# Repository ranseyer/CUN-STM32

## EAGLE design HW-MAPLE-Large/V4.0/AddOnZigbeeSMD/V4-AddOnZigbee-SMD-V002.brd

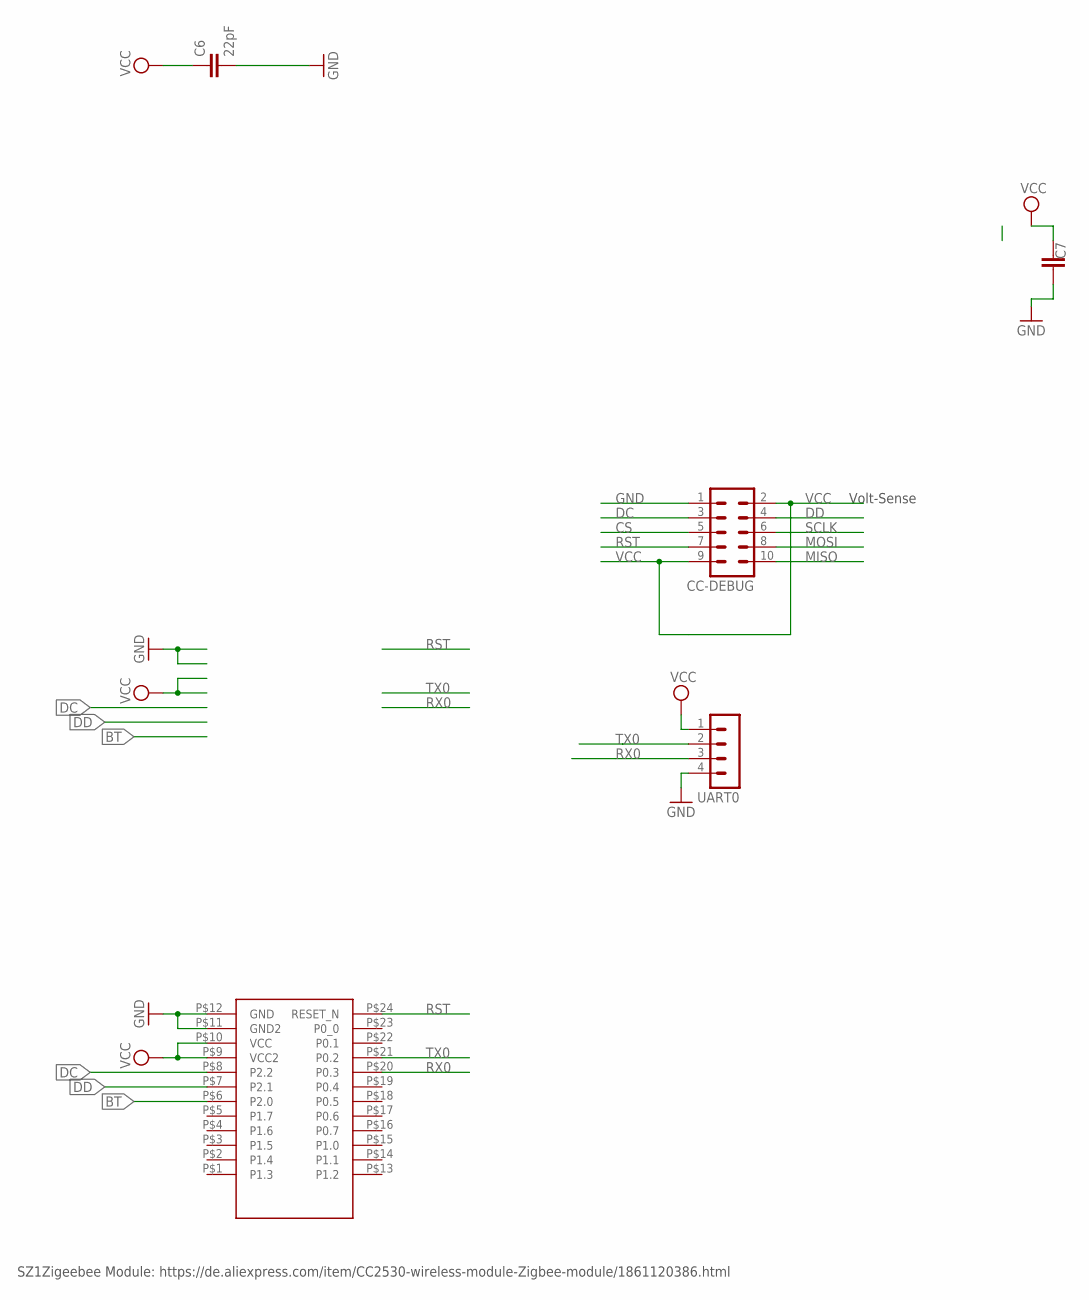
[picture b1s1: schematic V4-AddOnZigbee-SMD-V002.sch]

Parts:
C6: 22pF; C0805
C7: C-EUC1812; C1812
CC-DEBUG: MA05-2
U$1: CC2530; SZ1ZIGBEE-SMD
UART0: MA04-1

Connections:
BT: U$1.P$6 (P2.0)
CS: CC-DEBUG.5
DC: CC-DEBUG.3, U$1.P$8 (P2.2)
DD: CC-DEBUG.4, U$1.P$7 (P2.1)
GND: C6.2, C7.1, CC-DEBUG.1, U$1.P$11 (GND2), U$1.P$12 (GND), UART0.4
MISO: CC-DEBUG.10
MOSI: CC-DEBUG.8
RST: CC-DEBUG.7, U$1.P$24 (RESET_N)
RX0: U$1.P$20 (P0.3), UART0.3
SCLK: CC-DEBUG.6
TX0: U$1.P$21 (P0.2), UART0.2
VCC: C6.1, C7.2, CC-DEBUG.2, CC-DEBUG.9, U$1.P$9 (VCC2), U$1.P$10 (VCC), UART0.1

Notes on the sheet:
Volt-Sense
SZ1Zigeebee Module: https://de.aliexpress.com/item/CC2530-wireless-module-Zigbee-module/1861120386.html

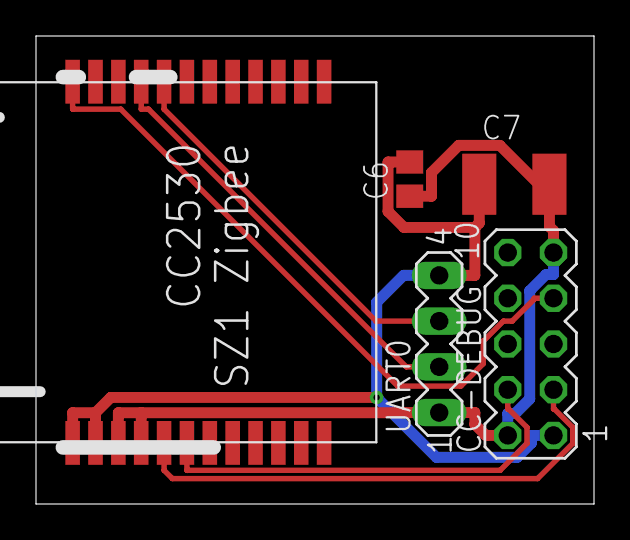
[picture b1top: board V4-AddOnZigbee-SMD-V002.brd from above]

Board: 2 copper layers, 31.0 x 26.0 mm, 5 parts (0 on the bottom side), 7 nets.

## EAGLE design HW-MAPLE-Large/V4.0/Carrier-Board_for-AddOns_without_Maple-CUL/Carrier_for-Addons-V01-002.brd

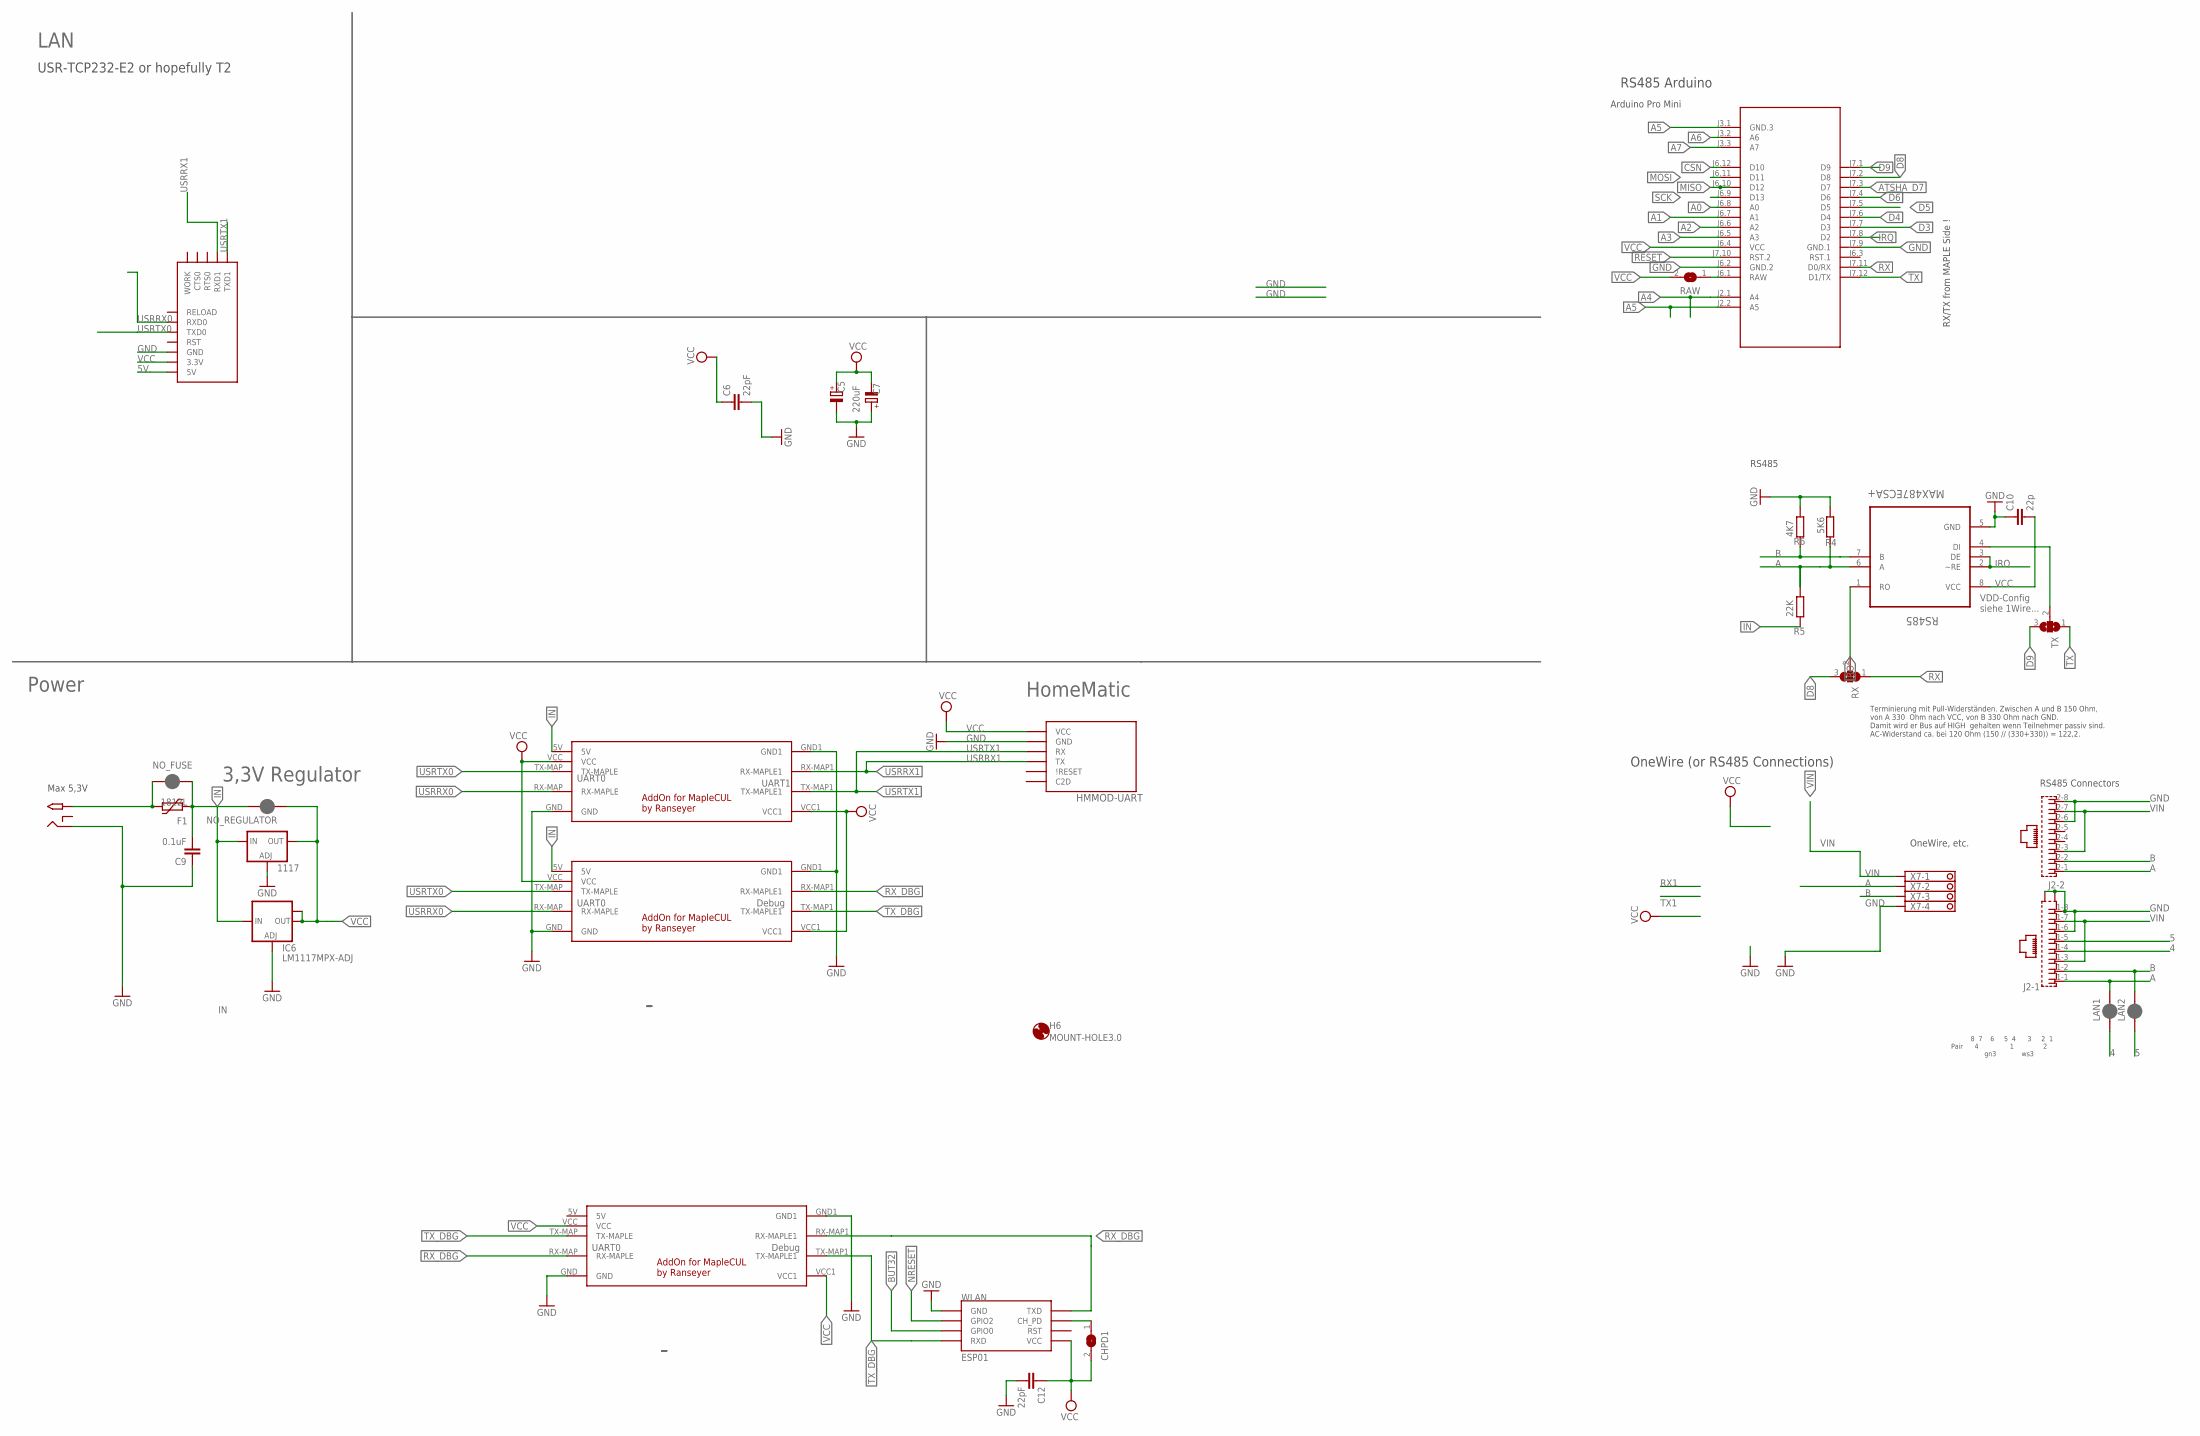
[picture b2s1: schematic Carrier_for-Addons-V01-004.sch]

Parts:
1117: LD117ADT50TR; DPACK
C5: 220uF; E5-8,5
C6, C12: 22pF; C0805
C7: CPOL-EUSMCE; SMC_E
C9: 0.1uF; C1206
C10: 22p; C0805
CHPD1: SJ
F1: 1812L
H6: MOUNT-HOLE3.0; 3,0
HMMOD-UART: HM-MOD-UARTDIL; HM-MOD-UART-DIL
IC6: LM1117MPX-ADJ; SOT223
J2: RJ45_2X_S
LAN1, LAN2: JUMPER-SMT_2_NC_PASTE_SILK; SMT-JUMPER_2_NC_PASTE_SILK
M1: ARDUINO-PRO-MINI-3.3V#NP; ARDUINO-PRO-MINI#NP
NO_FUSE: JUMPER-SMT_2_NC_PASTE_NO-SILK; SMT-JUMPER_2_NC_PASTE_NO-SILK
NO_REGULATOR: JUMPER-SMT_2_NC_PASTE_NO-SILK; SMT-JUMPER_2_NC_PASTE_NO-SILK
R4: 5K6; R0805
R5: 22K; R0805
R6: 4K7; R0805
RAW: SJ
RS485: MAX487ECSA+; SOIC127P600X175-8N
RX: SJ2W; SJ_2
TX: SJ2W; SJ_2
U$1, U$3, U$4: MAPLE-CUL-ADDON-V01; MAPLE-CUL-V01
U$2: 2.1MMJACKTHM; PJ-102A
U$5: USR-TCP232-E2
WLAN: ESP01
X7: 1751264

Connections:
4: J2.1-4 (4), LAN1.1
5: J2.1-5 (5), LAN2.1
5V.: U$5.5V
A: J2.1-1 (1), J2.2-1 (1), LAN1.2, R4.2, R5.2, RS485.6 (A), X7.2
A0: M1.J6.8 (A0)
A1: M1.J6.7 (A1)
A2: M1.J6.6 (A2)
A3: M1.J6.5 (A3)
A4: M1.J2.1 (A4)
A5: M1.J2.2 (A5), M1.J3.1 (GND.3)
A6: M1.J3.2 (A6)
A7: M1.J3.3 (A7)
ATSHA_D7: M1.J7.3 (D7)
B: J2.1-2 (2), J2.2-2 (2), LAN2.2, R6.1, RS485.7 (B), X7.3
BUT32: WLAN.GPIO0
CSN: M1.J6.12 (D10)
D3: M1.J7.7 (D3)
D4: M1.J7.6 (D4)
D5: M1.J7.5 (D5)
D6: M1.J7.4 (D6)
D8: M1.J7.2 (D8), RX.3
D9: M1.J7.1 (D9), TX.3
DI1: RS485.4 (DI), TX.2
GND: 1117.1 (ADJ), C5.-, C6.2, C7.+, C9.1, C10.1, C12.2, HMMOD-UART.2 (GND), IC6.1 (ADJ), J2.1-6 (6), J2.1-8 (8), J2.2-6 (6), J2.2-8 (8), J2.G1 (S2), J2.G3 (S1), M1.J6.2 (GND.2), M1.J7.9 (GND.1), R4.1, R6.2, RS485.5 (GND), U$1.GND, U$1.GND1, U$2.RING, U$3.GND, U$3.GND1, U$4.GND, U$4.GND1, U$5.GND, WLAN.GND, X7.4
IN: 1117.3 (IN), C9.2, F1.P$1 (1), IC6.3 (IN), NO_FUSE.1, NO_REGULATOR.2, R5.1, U$3.5V, U$4.5V
IRQ: M1.J7.8 (D2), RS485.2 (~RE), RS485.3 (DE)
MISO: M1.J6.10 (D12)
MOSI: M1.J6.11 (D11)
unnamed: CHPD1.1, WLAN.CH_PD
NRESET: WLAN.GPIO2
RAW1: M1.J6.1 (RAW), RAW.1
RESET: M1.J7.10 (RST.2)
RO: RS485.1 (RO), RX.2
RX: M1.J7.11 (D0/RX), RX.1
RX_DBG: U$1.RX-MAP (RX-MAPLE), U$1.RX-MAP1 (RX-MAPLE1), U$4.RX-MAP1 (RX-MAPLE1), WLAN.TX (TXD)
SCK: M1.J6.9 (D13)
TX: M1.J7.12 (D1/TX), TX.1
TX_DBG: U$1.TX-MAP (TX-MAPLE), U$1.TX-MAP1 (TX-MAPLE1), U$4.TX-MAP1 (TX-MAPLE1), WLAN.RX (RXD)
USRRX0: U$3.RX-MAP (RX-MAPLE), U$4.RX-MAP (RX-MAPLE), U$5.RXD0
USRRX1: HMMOD-UART.5 (TX), U$3.RX-MAP1 (RX-MAPLE1), U$5.RXD1
USRTX0: U$3.TX-MAP (TX-MAPLE), U$4.TX-MAP (TX-MAPLE), U$5.TXD0
USRTX1: HMMOD-UART.6 (RX), U$3.TX-MAP1 (TX-MAPLE1), U$5.TXD1
VCC: 1117.4 (OUT), C5.+, C6.1, C7.-, C10.2, C12.1, CHPD1.2, HMMOD-UART.1 (VCC), IC6.2 (OUT), IC6.TAB (OUT1), M1.J6.4 (VCC), NO_REGULATOR.1, RAW.2, RS485.8 (VCC), U$1.VCC, U$1.VCC1, U$3.VCC, U$3.VCC1, U$4.VCC, U$4.VCC1, U$5.3.3V, WLAN.VCC
VIN: F1.P$2 (2), J2.1-3 (3), J2.1-7 (7), J2.2-3 (3), J2.2-7 (7), NO_FUSE.2, U$2.TIP, X7.1

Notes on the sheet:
Power
HomeMatic
LAN
UART0
Debug
UART1
RX/TX from MAPLE Side !
8 7 6 5 4 3 2 1 Pair 4 1 2 gn3 ws3
RS485 Connectors
OneWire, etc.
Arduino Pro Mini
RS485
VDD-Config siehe 1Wire...
Terminierung mit Pull-Widerständen. Zwischen A und B 150 Ohm, von A 330 Ohm nach VCC, von B 330 Ohm nach GND. Damit wird er Bus auf HIGH gehalten wenn Teilnehmer passiv sind. AC-Widerstand ca. bei 120 Ohm (150 // (330+330)) = 122,2.
OneWire (or RS485 Connections)
USR-TCP232-E2 or hopefully T2
RS485 Arduino
Max 5,3V
3,3V Regulator

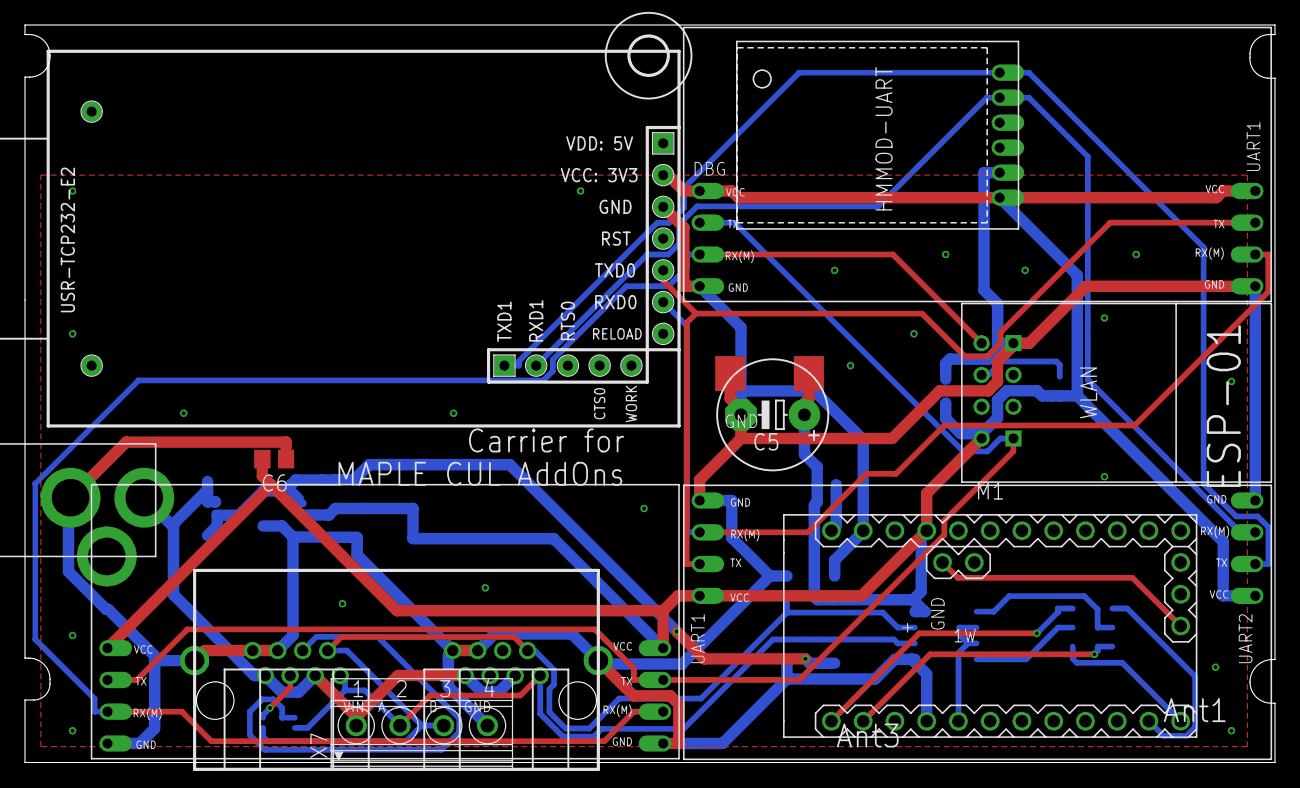
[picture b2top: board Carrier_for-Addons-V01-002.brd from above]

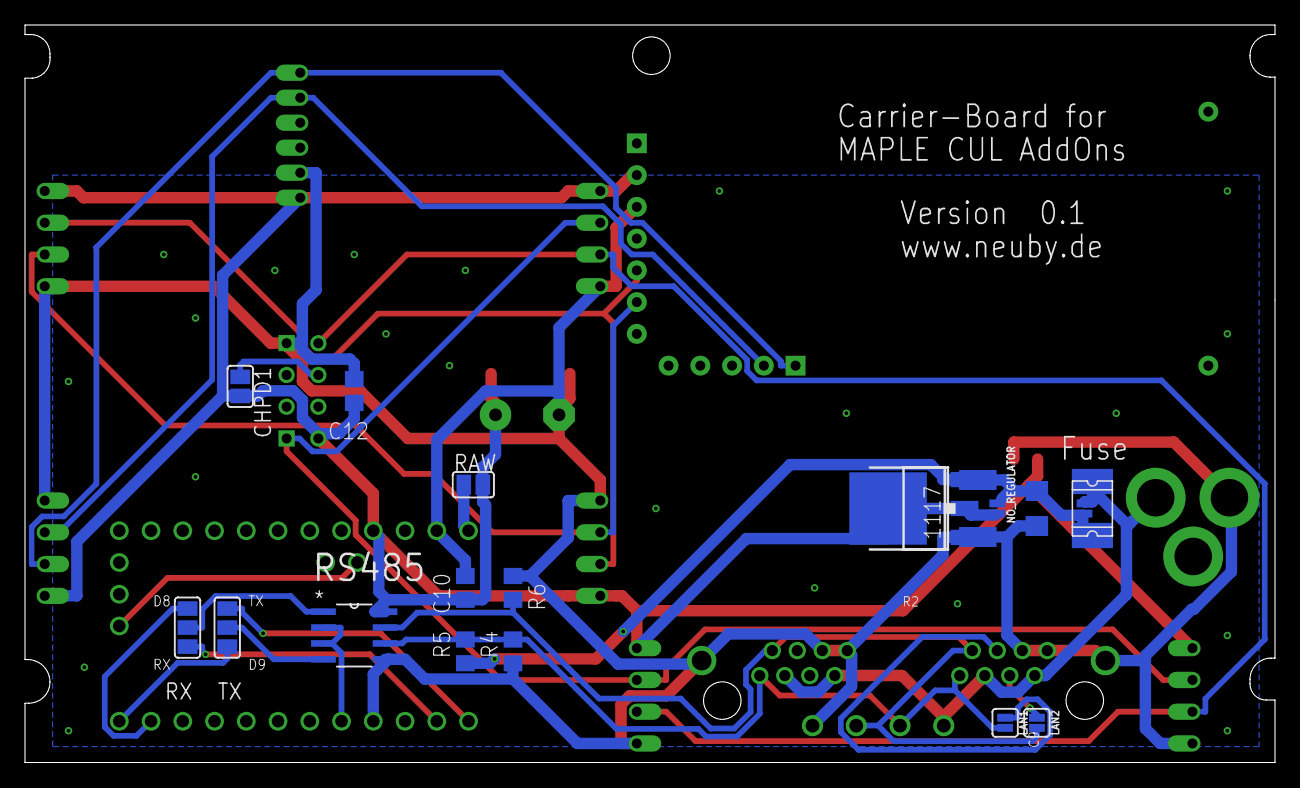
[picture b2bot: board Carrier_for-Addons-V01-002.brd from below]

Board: 2 copper layers, 100.0 x 59.0 mm, 32 parts (18 on the bottom side), 24 nets.

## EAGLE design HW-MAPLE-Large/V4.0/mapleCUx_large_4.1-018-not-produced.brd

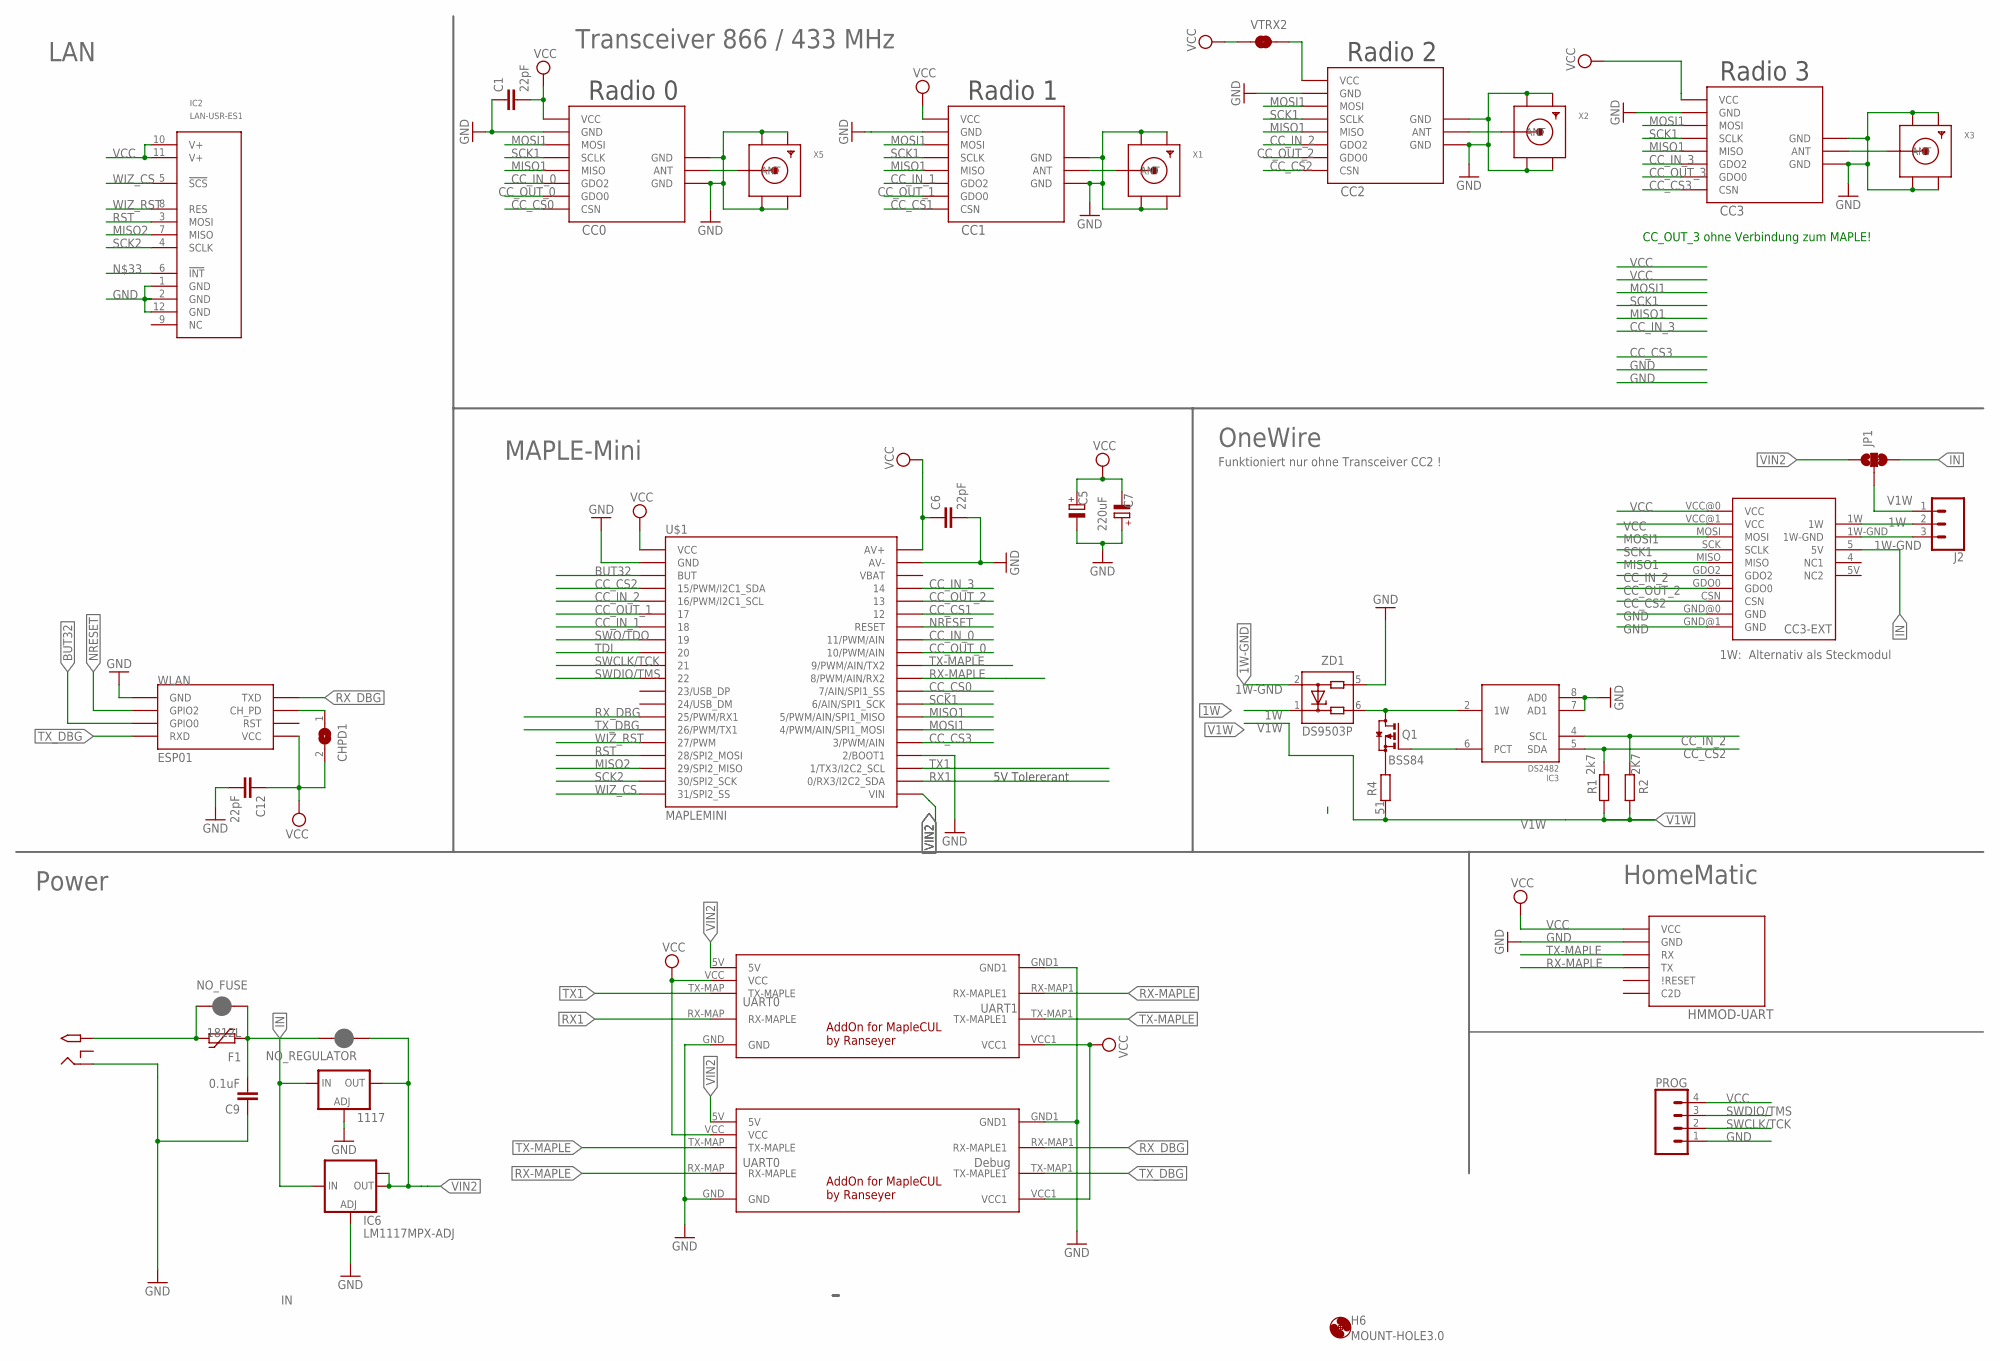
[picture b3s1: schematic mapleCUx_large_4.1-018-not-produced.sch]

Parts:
1117: LD117ADT50TR; DPACK
C1, C6, C12: 22pF; C0805
C5: 220uF; E5-8,5
C7: CPOL-EUSMCE; SMC_E
C9: 0.1uF; C1206
CC0: CC1101; CC1101_MODULE1_SMD
CC1, CC2, CC3: CC1101_MODULE1SMD; CC1101_MODULE1_SMD
CC3-EXT: ONEWIRE-MODULE; ONEWIRE_CC1101_MODULE3_DIL
CHPD1: SJ
F1: 1812L
H6: MOUNT-HOLE3.0; 3,0
HMMOD-UART: HM-MOD-UARTDIL; HM-MOD-UART-DIL
IC2: LAN-USR-ES1; USR-ES1
IC3: DS2482; SO08
IC6: LM1117MPX-ADJ; SOT223
J2: CONN_03LONGPADS; 1X03_LONGPADS
JP1: JUMPER-SMT_3_1-NC_TRACE_SILK; SMT-JUMPER_3_1-NC_TRACE_SILK
NO_FUSE: JUMPER-SMT_2_NC_PASTE_NO-SILK; SMT-JUMPER_2_NC_PASTE_NO-SILK
NO_REGULATOR: JUMPER-SMT_2_NC_PASTE_NO-SILK; SMT-JUMPER_2_NC_PASTE_NO-SILK
PROG: CONN_04LOCK; 1X04_LOCK
Q1: BSS84; SOT23
R1: 2k7; R0805
R2: 2K7; R0805
R4: 51; R0805
U$1: MAPLEMINI; 20-DIP
U$2: 2.1MMJACKTHM; PJ-102A
U$3, U$4: MAPLE-CUL-ADDON-V01; MAPLE-CUL-V01
VTRX2: JUMPER-SMT_2_NC_TRACE_SILK; SMT-JUMPER_2_NC_TRACE_SILK
WLAN: ESP01
X1, X2, X3, X5: SMACONNECTOR_EDGE; SMA_EDGELAUNCH
ZD1: DS9503P; TSOC6

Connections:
1W: CC3-EXT.1W, J2.2, ZD1.1
1W-GND: CC3-EXT.1W-GND, J2.3, ZD1.2
ANT0: CC0.ANT, X5.P (ANT)
ANT1: CC1.ANT, X1.P (ANT)
ANT2: CC2.ANT, X2.P (ANT)
ANT3: CC3.ANT, X3.P (ANT)
BUT32: U$1.3 (BUT), WLAN.GPIO0
CC_CS0: CC0.CSN, U$1.29 (7/AIN/SPI1_SS)
CC_CS1: CC1.CSN, U$1.35 (12)
CC_CS2: CC2.CSN, CC3-EXT.CSN, IC3.5 (SDA), R1.2, U$1.4 (15/PWM/I2C1_SDA)
CC_CS3: CC3.CSN, U$1.25 (3/PWM/AIN)
CC_IN_0: CC0.GDO2, U$1.33 (11/PWM/AIN)
CC_IN_1: CC1.GDO2, U$1.7 (18)
CC_IN_2: CC2.GDO2, CC3-EXT.GDO2, IC3.4 (SCL), R2.2, U$1.5 (16/PWM/I2C1_SCL)
CC_IN_3: CC3.GDO2, U$1.37 (14)
CC_OUT_0: CC0.GDO0, U$1.32 (10/PWM/AIN)
CC_OUT_1: CC1.GDO0, U$1.6 (17)
CC_OUT_2: CC2.GDO0, CC3-EXT.GDO0, U$1.36 (13)
CC_OUT_3: CC3.GDO0
GND: 1117.1 (ADJ), C1.1, C5.-, C6.2, C7.+, C9.1, C12.2, CC0.GND@0 (GND), CC0.GND@1 (GND), CC0.GND@2 (GND), CC1.GND@0 (GND), CC1.GND@1 (GND), CC1.GND@2 (GND), CC2.GND@0 (GND), CC2.GND@1 (GND), CC2.GND@2 (GND), CC3.GND@0 (GND), CC3.GND@1 (GND), CC3.GND@2 (GND), CC3-EXT.GND@0 (GND), CC3-EXT.GND@1 (GND), HMMOD-UART.2 (GND), IC2.1 (GND), IC2.2 (GND), IC2.12 (GND), IC3.3 (GND), IC3.7 (AD1), IC3.8 (AD0), IC6.1 (ADJ), PROG.1, U$1.2 (GND), U$1.24 (2/BOOT1), U$1.39 (AV-), U$2.RING, U$3.GND, U$3.GND1, U$4.GND, U$4.GND1, WLAN.GND, X1.GND@1 (GND4), X1.GND@2 (GND3), X1.GND@3 (GND2), X1.GND@4 (GND1), X2.GND@1 (GND4), X2.GND@2 (GND3), X2.GND@3 (GND2), X2.GND@4 (GND1), X3.GND@1 (GND4), X3.GND@2 (GND3), X3.GND@3 (GND2), X3.GND@4 (GND1), X5.GND@1 (GND4), X5.GND@2 (GND3), X5.GND@3 (GND2), X5.GND@4 (GND1), ZD1.5
IN: 1117.3 (IN), C9.2, CC3-EXT.5 (5V), F1.P$1 (1), IC6.3 (IN), JP1.3, NO_FUSE.1, NO_REGULATOR.2
MISO1: CC0.MISO, CC1.MISO, CC2.MISO, CC3.MISO, CC3-EXT.MISO, U$1.27 (5/PWM/AIN/SPI1_MISO)
MISO2: IC2.7 (MISO), U$1.18 (29/SPI2_MISO)
MOSI1: CC0.MOSI, CC1.MOSI, CC2.MOSI, CC3.MOSI, CC3-EXT.MOSI, U$1.26 (4/PWM/AIN/SPI1_MOSI)
unnamed: CC2.VCC, VTRX2.2
unnamed: CHPD1.1, WLAN.CH_PD
unnamed: IC3.6 (PCT), Q1.1 (G)
unnamed: IC3.2 (1W), Q1.3 (D), ZD1.6
unnamed: Q1.2 (S), R4.1
NRESET: U$1.34 (RESET), WLAN.GPIO2
RST: IC2.3 (MOSI), U$1.17 (28/SPI2_MOSI)
RX1: U$1.22 (0/RX3/I2C2_SDA), U$3.RX-MAP (RX-MAPLE)
RX-MAPLE: HMMOD-UART.5 (TX), U$1.30 (8/PWM/AIN/RX2), U$3.RX-MAP1 (RX-MAPLE1), U$4.RX-MAP (RX-MAPLE)
RX_DBG: U$1.14 (25/PWM/RX1), U$4.RX-MAP1 (RX-MAPLE1), WLAN.TX (TXD)
SCK1: CC0.SCLK, CC1.SCLK, CC2.SCLK, CC3.SCLK, CC3-EXT.SCK (SCLK), U$1.28 (6/AIN/SPI1_SCK)
SCK2: IC2.4 (SCLK), U$1.19 (30/SPI2_SCK)
SWCLK/TCK: PROG.2, U$1.10 (21)
SWDIO/TMS: PROG.3, U$1.11 (22)
SWO/TDO: U$1.8 (19)
TDI: U$1.9 (20)
TX1: U$1.23 (1/TX3/I2C2_SCL), U$3.TX-MAP (TX-MAPLE)
TX-MAPLE: HMMOD-UART.6 (RX), U$1.31 (9/PWM/AIN/TX2), U$3.TX-MAP1 (TX-MAPLE1), U$4.TX-MAP (TX-MAPLE)
TX_DBG: U$1.15 (26/PWM/TX1), U$4.TX-MAP1 (TX-MAPLE1), WLAN.RX (RXD)
V1W: IC3.1 (VDD), J2.1, JP1.2, R1.1, R2.1, R4.2
VCC: C1.2, C5.+, C6.1, C7.-, C12.1, CC0.VCC, CC1.VCC, CC3.VCC, CC3-EXT.VCC@0 (VCC), CC3-EXT.VCC@1 (VCC), CHPD1.2, HMMOD-UART.1 (VCC), IC2.10 (V+), IC2.11 (V+), PROG.4, U$1.1 (VCC), U$1.40 (AV+), U$3.VCC, U$3.VCC1, U$4.VCC, U$4.VCC1, VTRX2.1, WLAN.VCC
VIN: F1.P$2 (2), NO_FUSE.2, U$2.TIP
VIN2: 1117.4 (OUT), IC6.2 (OUT), IC6.TAB (OUT1), JP1.1, NO_REGULATOR.1, U$1.21 (VIN), U$3.5V, U$4.5V
WIZ_CS: IC2.5 (!SCS!), U$1.20 (31/SPI2_SS)
WIZ_RST: IC2.8 (RES), U$1.16 (27/PWM)

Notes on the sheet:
Radio 1
Radio 0
Radio 2
Radio 3
OneWire
Power
HomeMatic
MAPLE-Mini
Transceiver 866 / 433 MHz
LAN
CC_OUT_3 ohne Verbindung zum MAPLE!
Funktioniert nur ohne Transceiver CC2 !
1W: Alternativ als Steckmodul
UART0
Debug
UART1
5V Tolererant

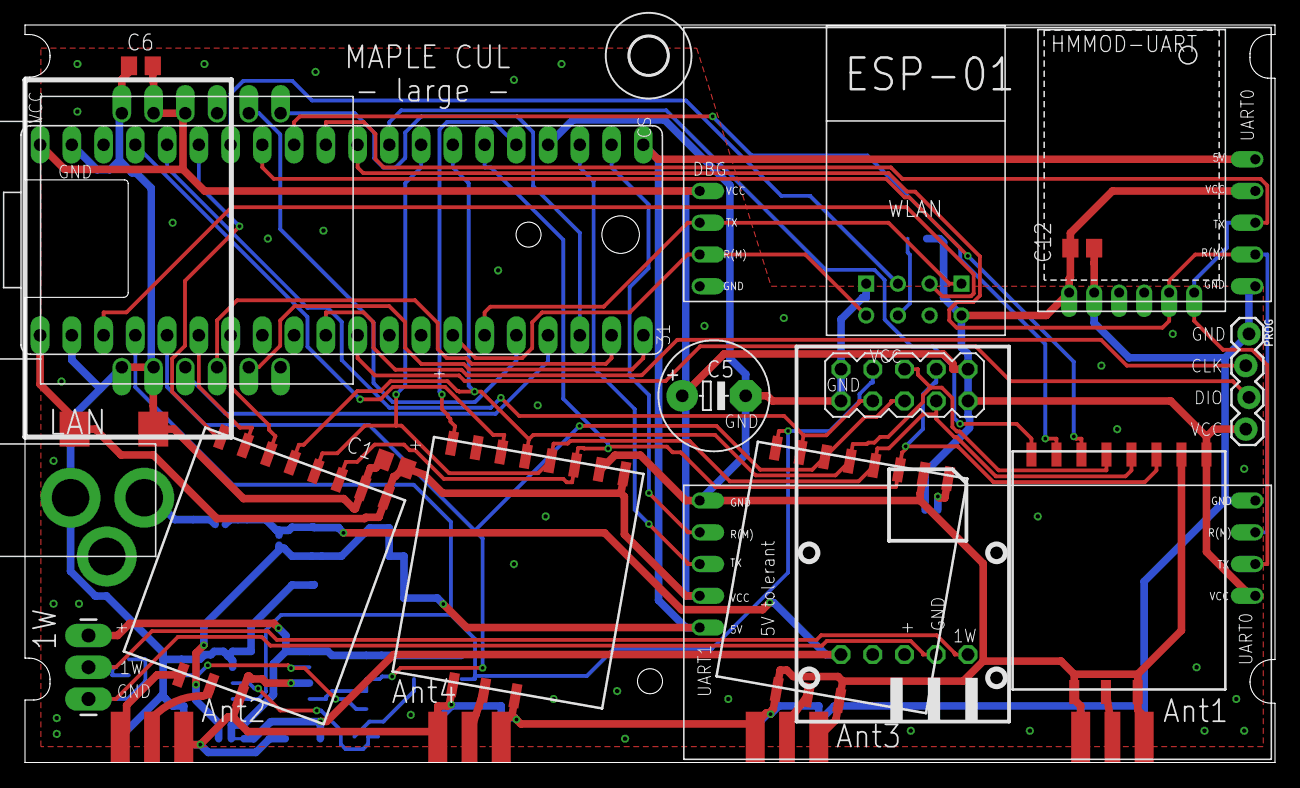
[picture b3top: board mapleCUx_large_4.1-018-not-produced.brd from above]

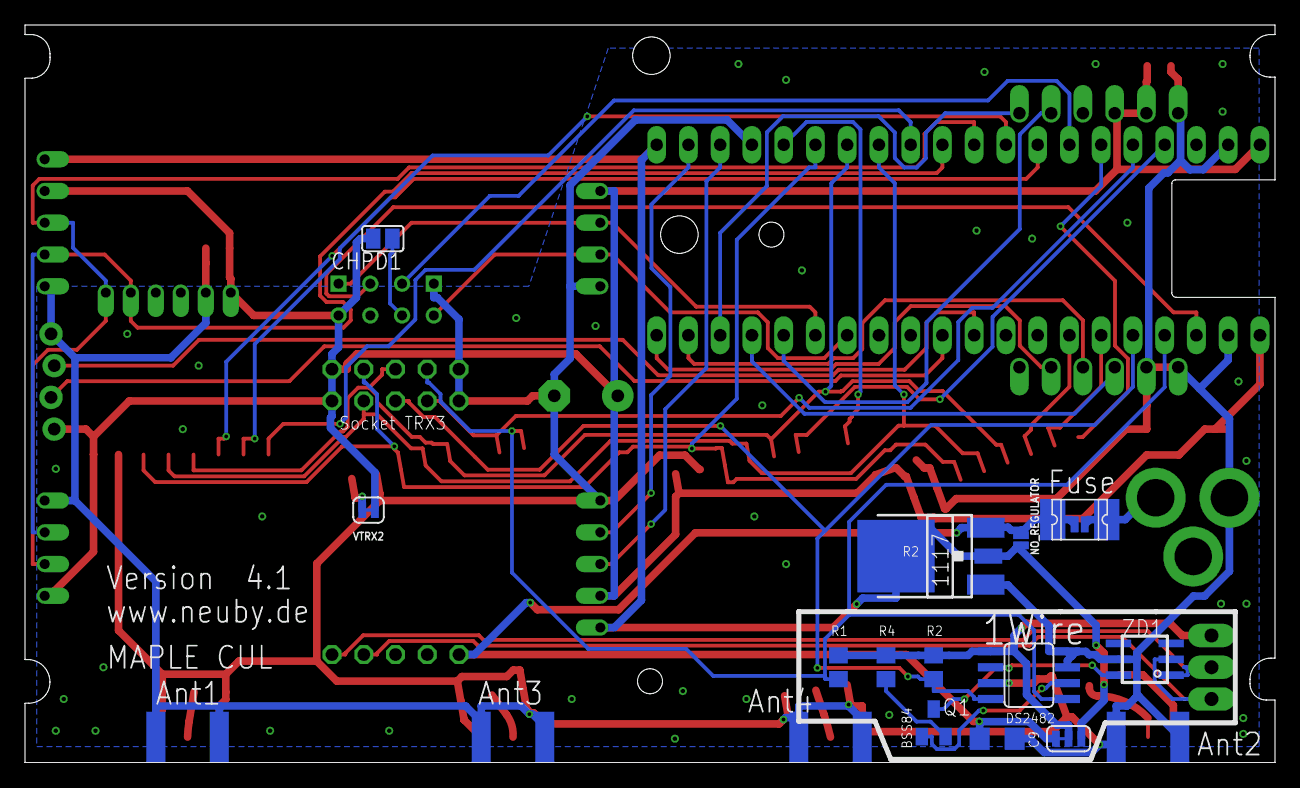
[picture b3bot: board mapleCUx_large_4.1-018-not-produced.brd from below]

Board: 2 copper layers, 100.0 x 59.0 mm, 39 parts (15 on the bottom side), 46 nets.

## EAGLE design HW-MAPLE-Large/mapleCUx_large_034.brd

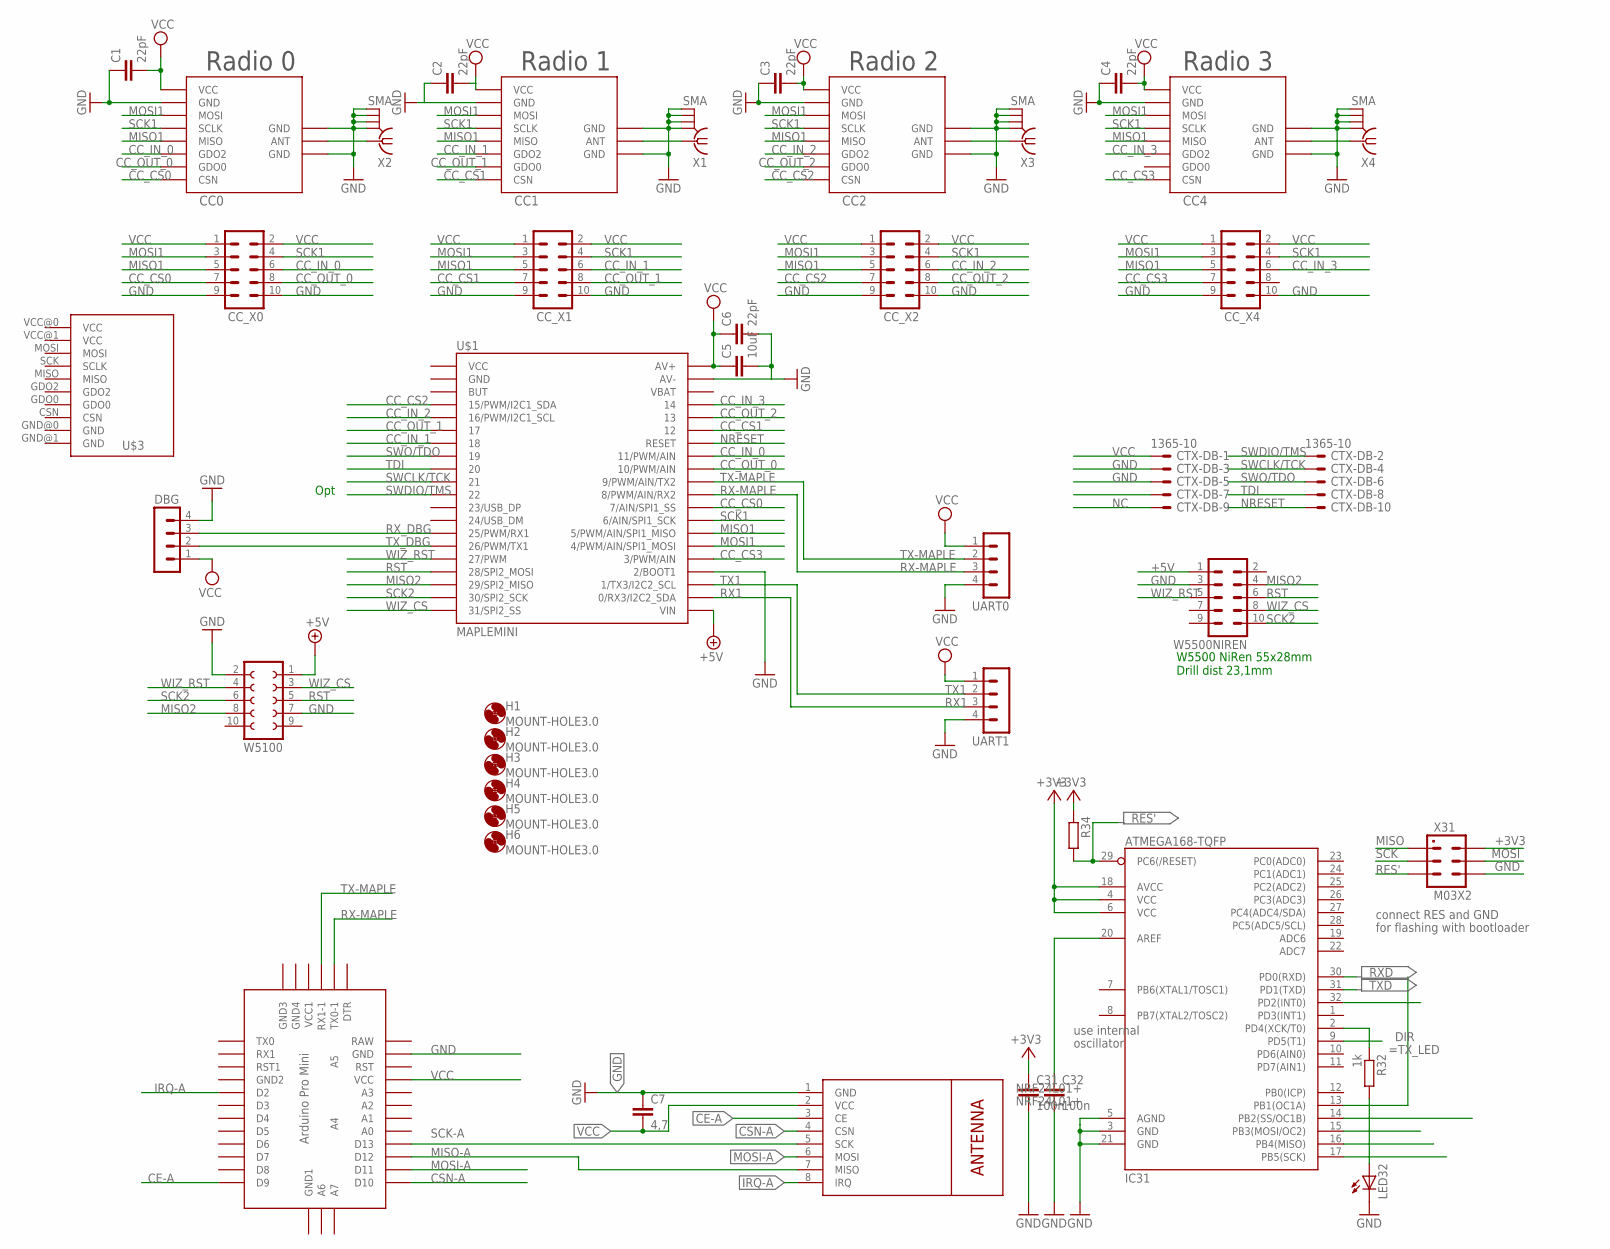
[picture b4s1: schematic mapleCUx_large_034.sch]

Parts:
C1, C2, C3, C4, C6: 22pF; C0805
C5: 10uF; C1210
C7: 4,7; C1210
C31, C32: 100n; C0805
CC0, CC1, CC2, CC4: CC1101_MODULE1SMD; CC1101_MODULE1_SMD
CC_X0, CC_X1, CC_X2, CC_X4: MA05-2
CTX-DB: 1365-10
DBG: MA04-1
H1, H2, H3, H4, H5, H6: MOUNT-HOLE3.0; 3,0
IC31: ATMEGA168-TQFP; TQFP32-08
LED32: LEDCHIPLED_0805; CHIPLED_0805
NRF24L01+: NRF24L01+; WIRELESS-NRF24L01
R32: 1k; R0805
R34: R-EU_R0805; R0805
U$1: MAPLEMINI; 20-DIP
U$2: ABK-PRO-MINI
U$3: CC1101_MODULE3_DIL
UART0, UART1: MA04-1
W5100: FE05-2
W5500NIREN: MA05-2
X1, X2, X3, X4: SMA
X31: M03X2; 2X03-1.27MM_SMD

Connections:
+3V3: C31.1, IC31.4 (VCC), IC31.6 (VCC), IC31.18 (AVCC), R34.1, X31.P$2 (2)
+5V: U$1.21 (VIN), W5100.1, W5500NIREN.1
CC_CS0: CC0.CSN, CC_X0.7, U$1.29 (7/AIN/SPI1_SS)
CC_CS1: CC1.CSN, CC_X1.7, U$1.35 (12)
CC_CS2: CC2.CSN, CC_X2.7, U$1.4 (15/PWM/I2C1_SDA)
CC_CS3: CC4.CSN, CC_X4.7, U$1.25 (3/PWM/AIN)
CC_IN_0: CC0.GDO2, CC_X0.6, U$1.33 (11/PWM/AIN)
CC_IN_1: CC1.GDO2, CC_X1.6, U$1.7 (18)
CC_IN_2: CC2.GDO2, CC_X2.6, U$1.5 (16/PWM/I2C1_SCL)
CC_IN_3: CC4.GDO2, CC_X4.6, U$1.37 (14)
CC_OUT_0: CC0.GDO0, CC_X0.8, U$1.32 (10/PWM/AIN)
CC_OUT_1: CC1.GDO0, CC_X1.8, U$1.6 (17)
CC_OUT_2: CC2.GDO0, CC_X2.8, U$1.36 (13)
CE-A: NRF24L01+.3 (CE), U$2.D9
CS: IC31.14 (PB2(SS/OC1B))
CSN-A: NRF24L01+.4 (CSN), U$2.D10
DIR: IC31.9 (PD5(T1))
GND: C1.1, C2.1, C3.1, C4.1, C5.2, C6.2, C7.1, C31.2, C32.2, CC0.GND@0 (GND), CC0.GND@1 (GND), CC0.GND@2 (GND), CC1.GND@0 (GND), CC1.GND@1 (GND), CC1.GND@2 (GND), CC2.GND@0 (GND), CC2.GND@1 (GND), CC2.GND@2 (GND), CC4.GND@0 (GND), CC4.GND@1 (GND), CC4.GND@2 (GND), CC_X0.9, CC_X0.10, CC_X1.9, CC_X1.10, CC_X2.9, CC_X2.10, CC_X4.9, CC_X4.10, CTX-DB.3, CTX-DB.5, DBG.4, IC31.3 (GND), IC31.5 (AGND), IC31.21 (GND), LED32.C, NRF24L01+.1 (GND), U$1.24 (2/BOOT1), U$1.39 (AV-), U$2.GND, U$3.GND@0 (GND), U$3.GND@1 (GND), UART0.4, UART1.4, W5100.2, W5100.7, W5500NIREN.3, X1.GND@1 (2), X1.GND@2 (3), X1.GND@3 (4), X1.GND@4 (5), X2.GND@1 (2), X2.GND@2 (3), X2.GND@3 (4), X2.GND@4 (5), X3.GND@1 (2), X3.GND@2 (3), X3.GND@3 (4), X3.GND@4 (5), X4.GND@1 (2), X4.GND@2 (3), X4.GND@3 (4), X4.GND@4 (5), X31.P$6 (6)
IRQ-A: NRF24L01+.8 (IRQ), U$2.D2
MISO: IC31.16 (PB4(MISO)), X31.P$1 (1)
MISO1: CC0.MISO, CC1.MISO, CC2.MISO, CC4.MISO, CC_X0.5, CC_X1.5, CC_X2.5, CC_X4.5, U$1.27 (5/PWM/AIN/SPI1_MISO)
MISO2: U$1.18 (29/SPI2_MISO), W5100.8, W5500NIREN.4
MISO-A: NRF24L01+.7 (MISO), U$2.D12
MOSI: IC31.15 (PB3(MOSI/OC2)), X31.P$4 (4)
MOSI1: CC0.MOSI, CC1.MOSI, CC2.MOSI, CC4.MOSI, CC_X0.3, CC_X1.3, CC_X2.3, CC_X4.3, U$1.26 (4/PWM/AIN/SPI1_MOSI)
MOSI-A: NRF24L01+.6 (MOSI), U$2.D11
unnamed: CC2.ANT, X3.1
unnamed: CC4.ANT, X4.1
unnamed: CC1.ANT, X1.1
unnamed: CC0.ANT, X2.1
unnamed: LED32.A, R32.2
unnamed: C32.1, IC31.20 (AREF)
NC: CTX-DB.9
NRESET: CTX-DB.10, U$1.34 (RESET)
RES': IC31.29 (PC6(/RESET)), R34.2, X31.P$5 (5)
RST: U$1.17 (28/SPI2_MOSI), W5100.5, W5500NIREN.6
RX1: U$1.22 (0/RX3/I2C2_SDA), UART1.3
RX-MAPLE: U$1.30 (8/PWM/AIN/RX2), U$2.TX0-1, UART0.3
RXD: IC31.30 (PD0(RXD))
RX_DBG: DBG.3, U$1.14 (25/PWM/RX1)
RX_LED: IC31.2 (PD4(XCK/T0)), R32.1
SCK: IC31.17 (PB5(SCK)), X31.P$3 (3)
SCK1: CC0.SCLK, CC1.SCLK, CC2.SCLK, CC4.SCLK, CC_X0.4, CC_X1.4, CC_X2.4, CC_X4.4, U$1.28 (6/AIN/SPI1_SCK)
SCK2: U$1.19 (30/SPI2_SCK), W5100.6, W5500NIREN.10
SCK-A: NRF24L01+.5 (SCK), U$2.D13
SWCLK/TCK: CTX-DB.4, U$1.10 (21)
SWDIO/TMS: CTX-DB.2, U$1.11 (22)
SWO/TDO: CTX-DB.6, U$1.8 (19)
TDI: CTX-DB.8, U$1.9 (20)
TX1: U$1.23 (1/TX3/I2C2_SCL), UART1.2
TX-MAPLE: U$1.31 (9/PWM/AIN/TX2), U$2.RX1-1, UART0.2
TXD: IC31.31 (PD1(TXD))
TX_DBG: DBG.2, U$1.15 (26/PWM/TX1)
VCC: C1.2, C2.2, C3.2, C4.2, C5.1, C6.1, C7.2, CC0.VCC, CC1.VCC, CC2.VCC, CC4.VCC, CC_X0.1, CC_X0.2, CC_X1.1, CC_X1.2, CC_X2.1, CC_X2.2, CC_X4.1, CC_X4.2, CTX-DB.1, DBG.1, NRF24L01+.2 (VCC), U$1.40 (AV+), U$2.VCC, U$3.VCC@0 (VCC), U$3.VCC@1 (VCC), UART0.1, UART1.1
WIZ_CS: U$1.20 (31/SPI2_SS), W5100.3, W5500NIREN.8
WIZ_RST: U$1.16 (27/PWM), W5100.4, W5500NIREN.5

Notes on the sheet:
Radio 1
Radio 0
Opt
Radio 2
Radio 3
W5500 NiRen 55x28mm Drill dist 23,1mm
use internal
oscillator
=TX_LED
connect RES and GND
for flashing with bootloader

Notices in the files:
parts and their libraries:
SparkFun-Jumpers: Licensing: Creative Commons ShareAlike 4.0 International - https://creativecommons.org/licenses/by-sa/4.0
diy-modules: Released under the Creative Commons Attribution 4.0 International License: http://creativecommons.org/licenses/by/4.0
